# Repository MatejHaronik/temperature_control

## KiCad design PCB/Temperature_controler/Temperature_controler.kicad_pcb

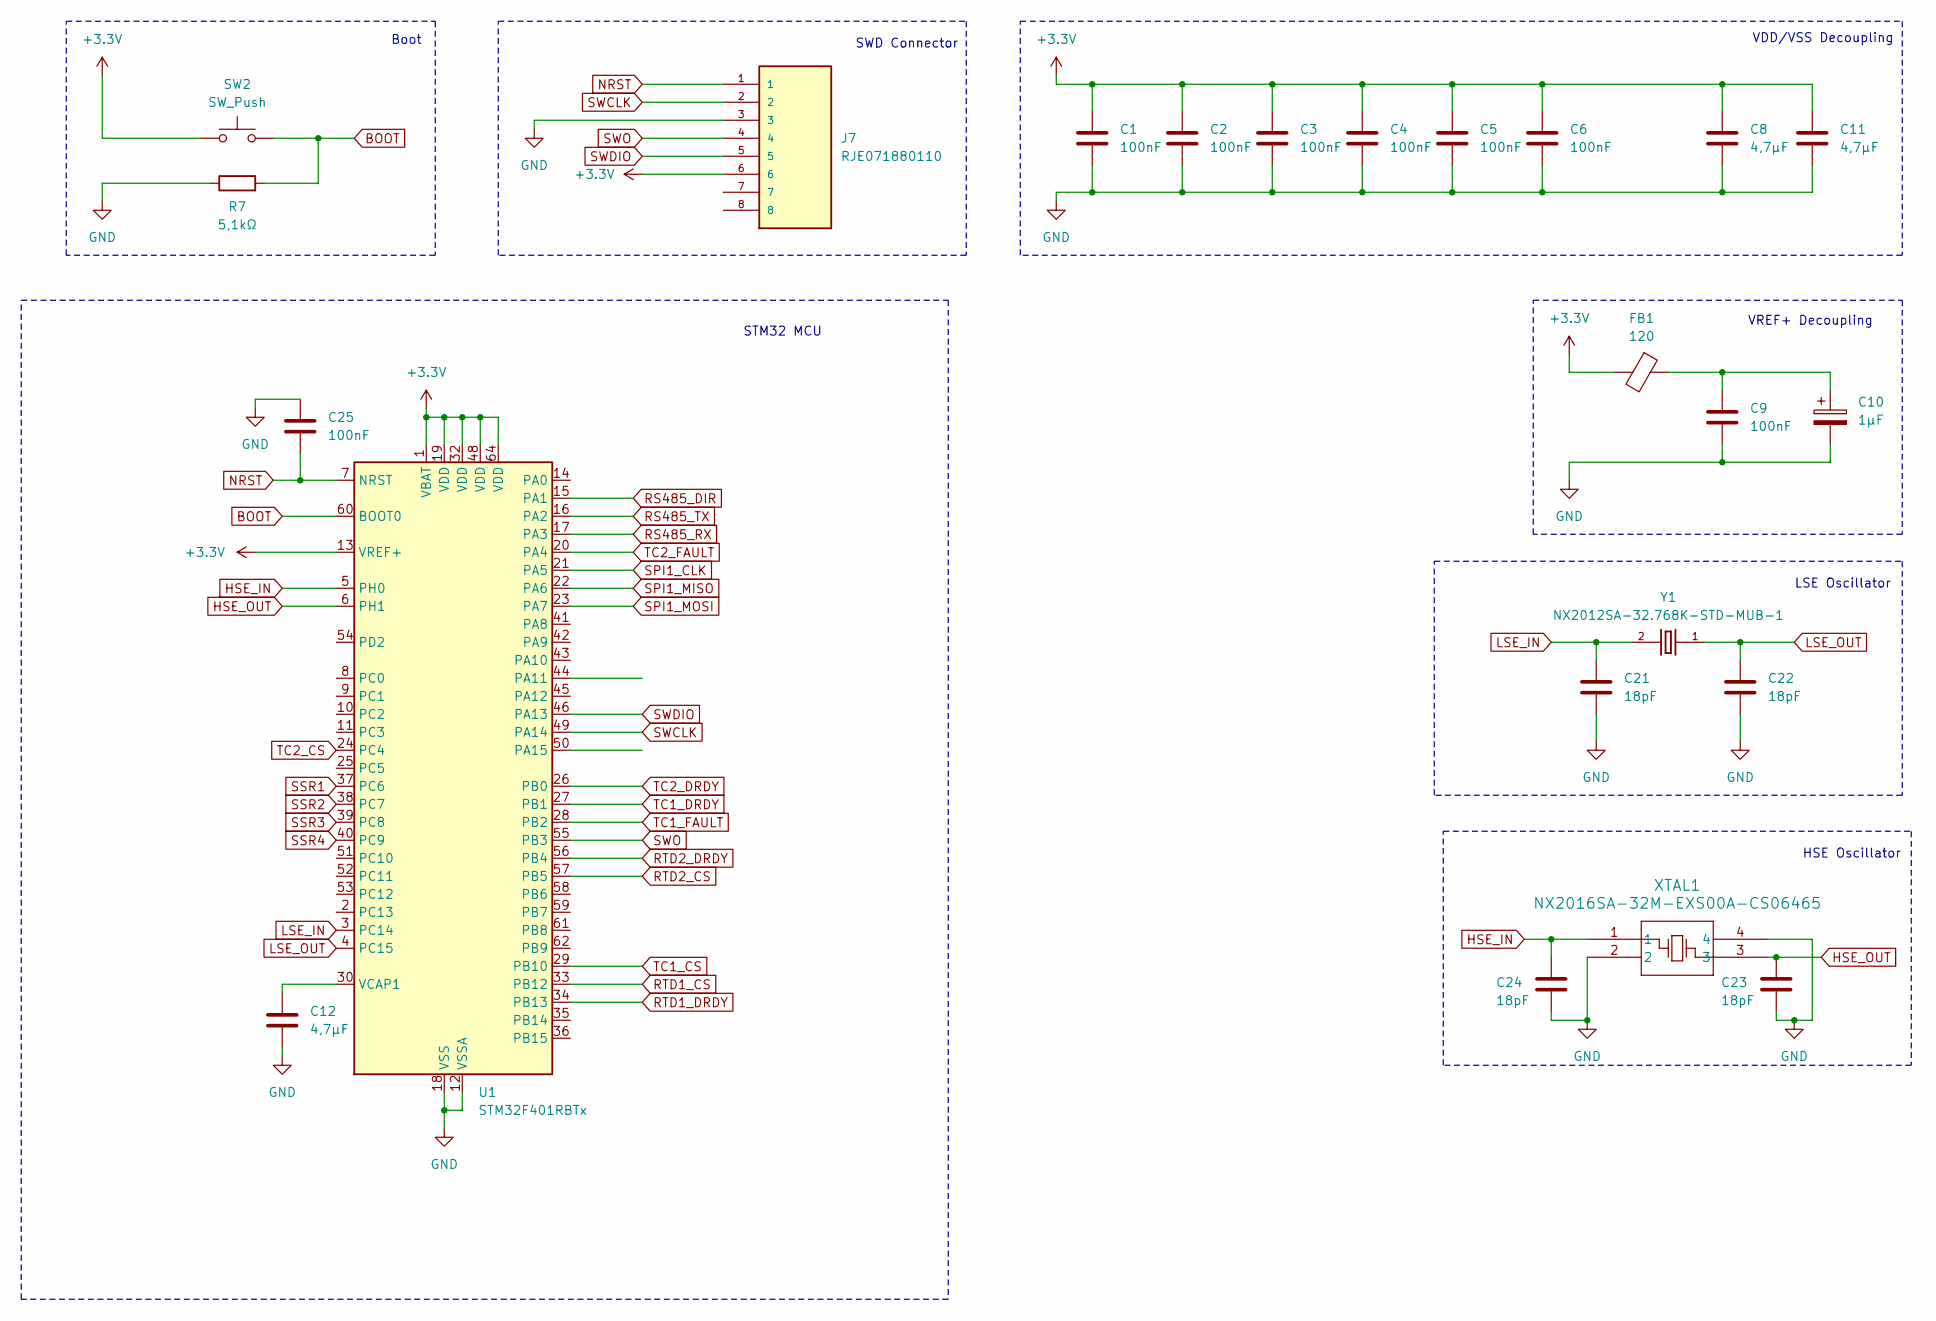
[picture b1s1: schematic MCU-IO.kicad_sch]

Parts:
C1, C2, C3, C4, C5, C6, C9, C25: 100nF; C_0805_2012Metric_Pad1.18x1.45mm_HandSolder
C8, C11, C12: 4,7µF; C_0805_2012Metric_Pad1.18x1.45mm_HandSolder
C10: 1µF; C_0805_2012Metric_Pad1.18x1.45mm_HandSolder
C21, C22, C23, C24: 18pF; C_0805_2012Metric_Pad1.18x1.45mm_HandSolder
FB1: 120; Fuse_2010_5025Metric_Pad1.52x2.65mm_HandSolder
J7: RJE071880110; AMPHENOL_RJE071880110; PARTREV C
R7: 5,1kΩ; R_0805_2012Metric_Pad1.20x1.40mm_HandSolder
SW2: SW_Push; SW_Push_1P1T-SH_NO_CK_KMR2xxG
U1: STM32F401RBTx; LQFP-64_10x10mm_P0.5mm
XTAL1: NX2016SA-32M-EXS00A-CS06465; NX2016SA_NDK
Y1: NX2012SA-32.768K-STD-MUB-1; XTAL_NX2012SA-32.768K-STD-MUB-1

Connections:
+3.3V: C1.1, C2.1, C3.1, C4.1, C5.1, C6.1, C8.1, C11.1, FB1.2, J7.6, SW2.1, U1.1 (VBAT), U1.13 (VREF+), U1.19 (VDD), U1.32 (VDD), U1.48 (VDD), U1.64 (VDD); also elsewhere on the board
BOOT: R7.2, SW2.2, U1.60 (BOOT0)
GND: C1.2, C2.2, C3.2, C4.2, C5.2, C6.2, C8.2, C9.2, C10.2, C11.2, C12.2, C21.2, C22.2, C23.2, C24.2, C25.1, J7.3, R7.1, U1.12 (VSSA), U1.18 (VSS), U1.31 (VSS), U1.47 (VSS), U1.63 (VSS), XTAL1.2, XTAL1.4; also elsewhere on the board
HSE_IN: C24.1, U1.5 (PH0), XTAL1.1
HSE_OUT: C23.1, U1.6 (PH1), XTAL1.3
LSE_IN: C21.1, U1.3 (PC14), Y1.2
LSE_OUT: C22.1, U1.4 (PC15), Y1.1
NRST: C25.2, J7.1, U1.7 (NRST)
unnamed: C9.1, C10.1, FB1.1
unnamed: C12.1, U1.30 (VCAP1)
RS485_DIR: U1.15 (PA1); also elsewhere on the board
RS485_RX: U1.17 (PA3); also elsewhere on the board
RS485_TX: U1.16 (PA2); also elsewhere on the board
RTD1_CS: U1.33 (PB12); also elsewhere on the board
RTD1_DRDY: U1.34 (PB13); also elsewhere on the board
RTD2_CS: U1.57 (PB5); also elsewhere on the board
RTD2_DRDY: U1.56 (PB4); also elsewhere on the board
SPI1_CLK: U1.21 (PA5); also elsewhere on the board
SPI1_MISO: U1.22 (PA6); also elsewhere on the board
SPI1_MOSI: U1.23 (PA7); also elsewhere on the board
SSR1: U1.37 (PC6); also elsewhere on the board
SSR2: U1.38 (PC7); also elsewhere on the board
SSR3: U1.39 (PC8); also elsewhere on the board
SSR4: U1.40 (PC9); also elsewhere on the board
SWCLK: J7.2, U1.49 (PA14)
SWDIO: J7.5, U1.46 (PA13)
SWO: J7.4, U1.55 (PB3)
TC1_CS: U1.29 (PB10); also elsewhere on the board
TC1_DRDY: U1.27 (PB1); also elsewhere on the board
TC1_FAULT: U1.28 (PB2); also elsewhere on the board
TC2_CS: U1.24 (PC4); also elsewhere on the board
TC2_DRDY: U1.26 (PB0); also elsewhere on the board
TC2_FAULT: U1.20 (PA4); also elsewhere on the board

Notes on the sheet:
HSE Oscillator
SWD Connector
LSE Oscillator
VREF+ Decoupling
Boot
STM32 MCU
VDD/VSS Decoupling

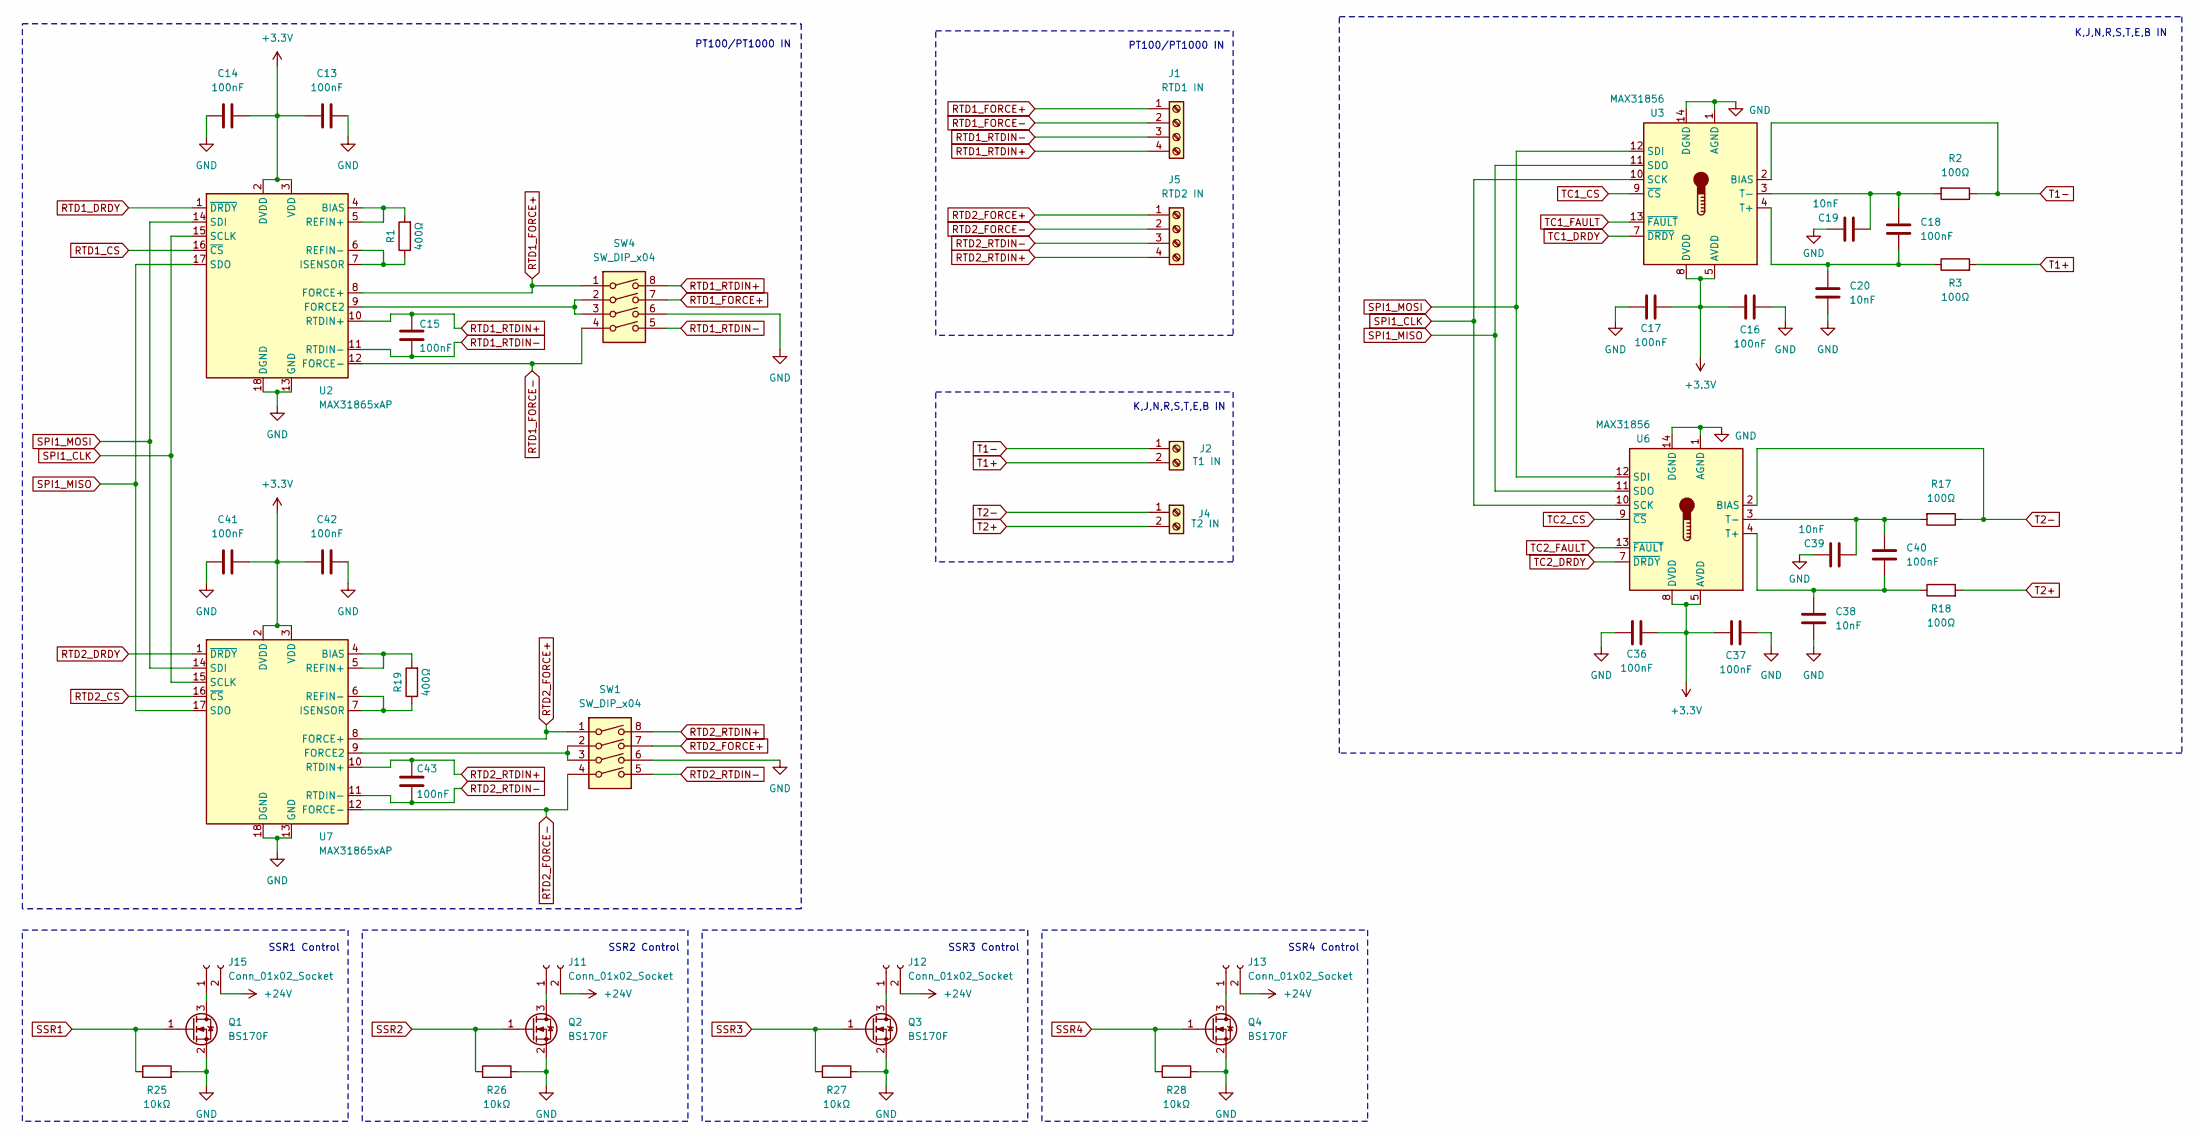
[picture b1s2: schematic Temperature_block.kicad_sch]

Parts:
C13, C14, C15, C16, C17, C18, C36, C37, C40, C41, C42, C43: 100nF; C_0805_2012Metric_Pad1.18x1.45mm_HandSolder
C19, C20, C38, C39: 10nF; C_0805_2012Metric_Pad1.18x1.45mm_HandSolder
J1: RTD1 IN; TerminalBlock_Phoenix_MKDS-1,5-4_1x04_P5.00mm_Horizontal
J2: T1 IN; TerminalBlock_Phoenix_MKDS-1,5-2_1x02_P5.00mm_Horizontal
J4: T2 IN; TerminalBlock_Phoenix_MKDS-1,5-2_1x02_P5.00mm_Horizontal
J5: RTD2 IN; TerminalBlock_Phoenix_MKDS-1,5-4_1x04_P5.00mm_Horizontal
J11, J12, J13, J15: Conn_01x02_Socket; SolderWire-1sqmm_1x02_P5.4mm_D1.4mm_OD2.7mm
Q1, Q2, Q3, Q4: BS170F; SOT-23
R1, R19: 400Ω; R_0805_2012Metric_Pad1.20x1.40mm_HandSolder
R2, R3, R17, R18: 100Ω; R_0805_2012Metric_Pad1.20x1.40mm_HandSolder
R25, R26, R27, R28: 10kΩ; R_0805_2012Metric_Pad1.20x1.40mm_HandSolder
SW1, SW4: SW_DIP_x04; SW_DIP_SPSTx04_Slide_Omron_A6H-4101_W6.15mm_P1.27mm
U2, U7: MAX31865xAP; SSOP-20_5.3x7.2mm_P0.65mm
U3, U6: MAX31856; TSSOP-14_4.4x5mm_P0.65mm

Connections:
+3.3V: C13.1, C14.1, C16.1, C17.1, C36.1, C37.1, C41.1, C42.1, U2.2 (DVDD), U2.3 (VDD), U3.5 (AVDD), U3.8 (DVDD), U6.5 (AVDD), U6.8 (DVDD), U7.2 (DVDD), U7.3 (VDD); also elsewhere on the board
+24V: J11.2, J12.2, J13.2, J15.2; also elsewhere on the board
GND: C13.2, C14.2, C16.2, C17.2, C19.1, C20.2, C36.2, C37.2, C38.2, C39.1, C41.2, C42.2, Q1.2 (S), Q2.2 (S), Q3.2 (S), Q4.2 (S), R25.2, R26.2, R27.2, R28.2, SW1.6, SW4.6, U2.13 (GND), U2.18 (DGND), U2.19 (GND), U3.1 (AGND), U3.14 (DGND), U6.1 (AGND), U6.14 (DGND), U7.13 (GND), U7.18 (DGND), U7.19 (GND); also elsewhere on the board
unnamed: J11.1, Q2.3 (D)
unnamed: J12.1, Q3.3 (D)
unnamed: J13.1, Q4.3 (D)
unnamed: J15.1, Q1.3 (D)
unnamed: R1.2, U2.4 (BIAS), U2.5 (REFIN+)
unnamed: SW4.2, SW4.3, U2.9 (FORCE2)
unnamed: R1.1, U2.6 (REFIN-), U2.7 (ISENSOR)
unnamed: C18.2, C20.1, R3.1, U3.4 (T+)
unnamed: C18.1, C19.2, R2.2, U3.3 (T-)
unnamed: C38.1, C40.2, R18.1, U6.4 (T+)
unnamed: C39.2, C40.1, R17.2, U6.3 (T-)
unnamed: R19.2, U7.4 (BIAS), U7.5 (REFIN+)
unnamed: SW1.2, SW1.3, U7.9 (FORCE2)
unnamed: R19.1, U7.6 (REFIN-), U7.7 (ISENSOR)
RTD1_CS: U2.16 (~CS); also elsewhere on the board
RTD1_DRDY: U2.1 (~DRDY); also elsewhere on the board
RTD1_FORCE+: J1.1, SW4.1, SW4.7, U2.8 (FORCE+)
RTD1_FORCE-: J1.2, SW4.4, U2.12 (FORCE-)
RTD1_RTDIN+: C15.2, J1.4, SW4.8, U2.10 (RTDIN+)
RTD1_RTDIN-: C15.1, J1.3, SW4.5, U2.11 (RTDIN-)
RTD2_CS: U7.16 (~CS); also elsewhere on the board
RTD2_DRDY: U7.1 (~DRDY); also elsewhere on the board
RTD2_FORCE+: J5.1, SW1.1, SW1.7, U7.8 (FORCE+)
RTD2_FORCE-: J5.2, SW1.4, U7.12 (FORCE-)
RTD2_RTDIN+: C43.2, J5.4, SW1.8, U7.10 (RTDIN+)
RTD2_RTDIN-: C43.1, J5.3, SW1.5, U7.11 (RTDIN-)
SPI1_CLK: U2.15 (SCLK), U3.10 (SCK), U6.10 (SCK), U7.15 (SCLK); also elsewhere on the board
SPI1_MISO: U2.17 (SDO), U3.11 (SDO), U6.11 (SDO), U7.17 (SDO); also elsewhere on the board
SPI1_MOSI: U2.14 (SDI), U3.12 (SDI), U6.12 (SDI), U7.14 (SDI); also elsewhere on the board
SSR1: Q1.1 (G), R25.1; also elsewhere on the board
SSR2: Q2.1 (G), R26.1; also elsewhere on the board
SSR3: Q3.1 (G), R27.1; also elsewhere on the board
SSR4: Q4.1 (G), R28.1; also elsewhere on the board
T1+: J2.2, R3.2
T1-: J2.1, R2.1, U3.2 (BIAS)
T2+: J4.2, R18.2
T2-: J4.1, R17.1, U6.2 (BIAS)
TC1_CS: U3.9 (~CS); also elsewhere on the board
TC1_DRDY: U3.7 (~DRDY); also elsewhere on the board
TC1_FAULT: U3.13 (~FAULT); also elsewhere on the board
TC2_CS: U6.9 (~CS); also elsewhere on the board
TC2_DRDY: U6.7 (~DRDY); also elsewhere on the board
TC2_FAULT: U6.13 (~FAULT); also elsewhere on the board

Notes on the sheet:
K,J,N,R,S,T,E,B IN
PT100/PT1000 IN
SSR2 Control
SSR4 Control
SSR3 Control
SSR1 Control

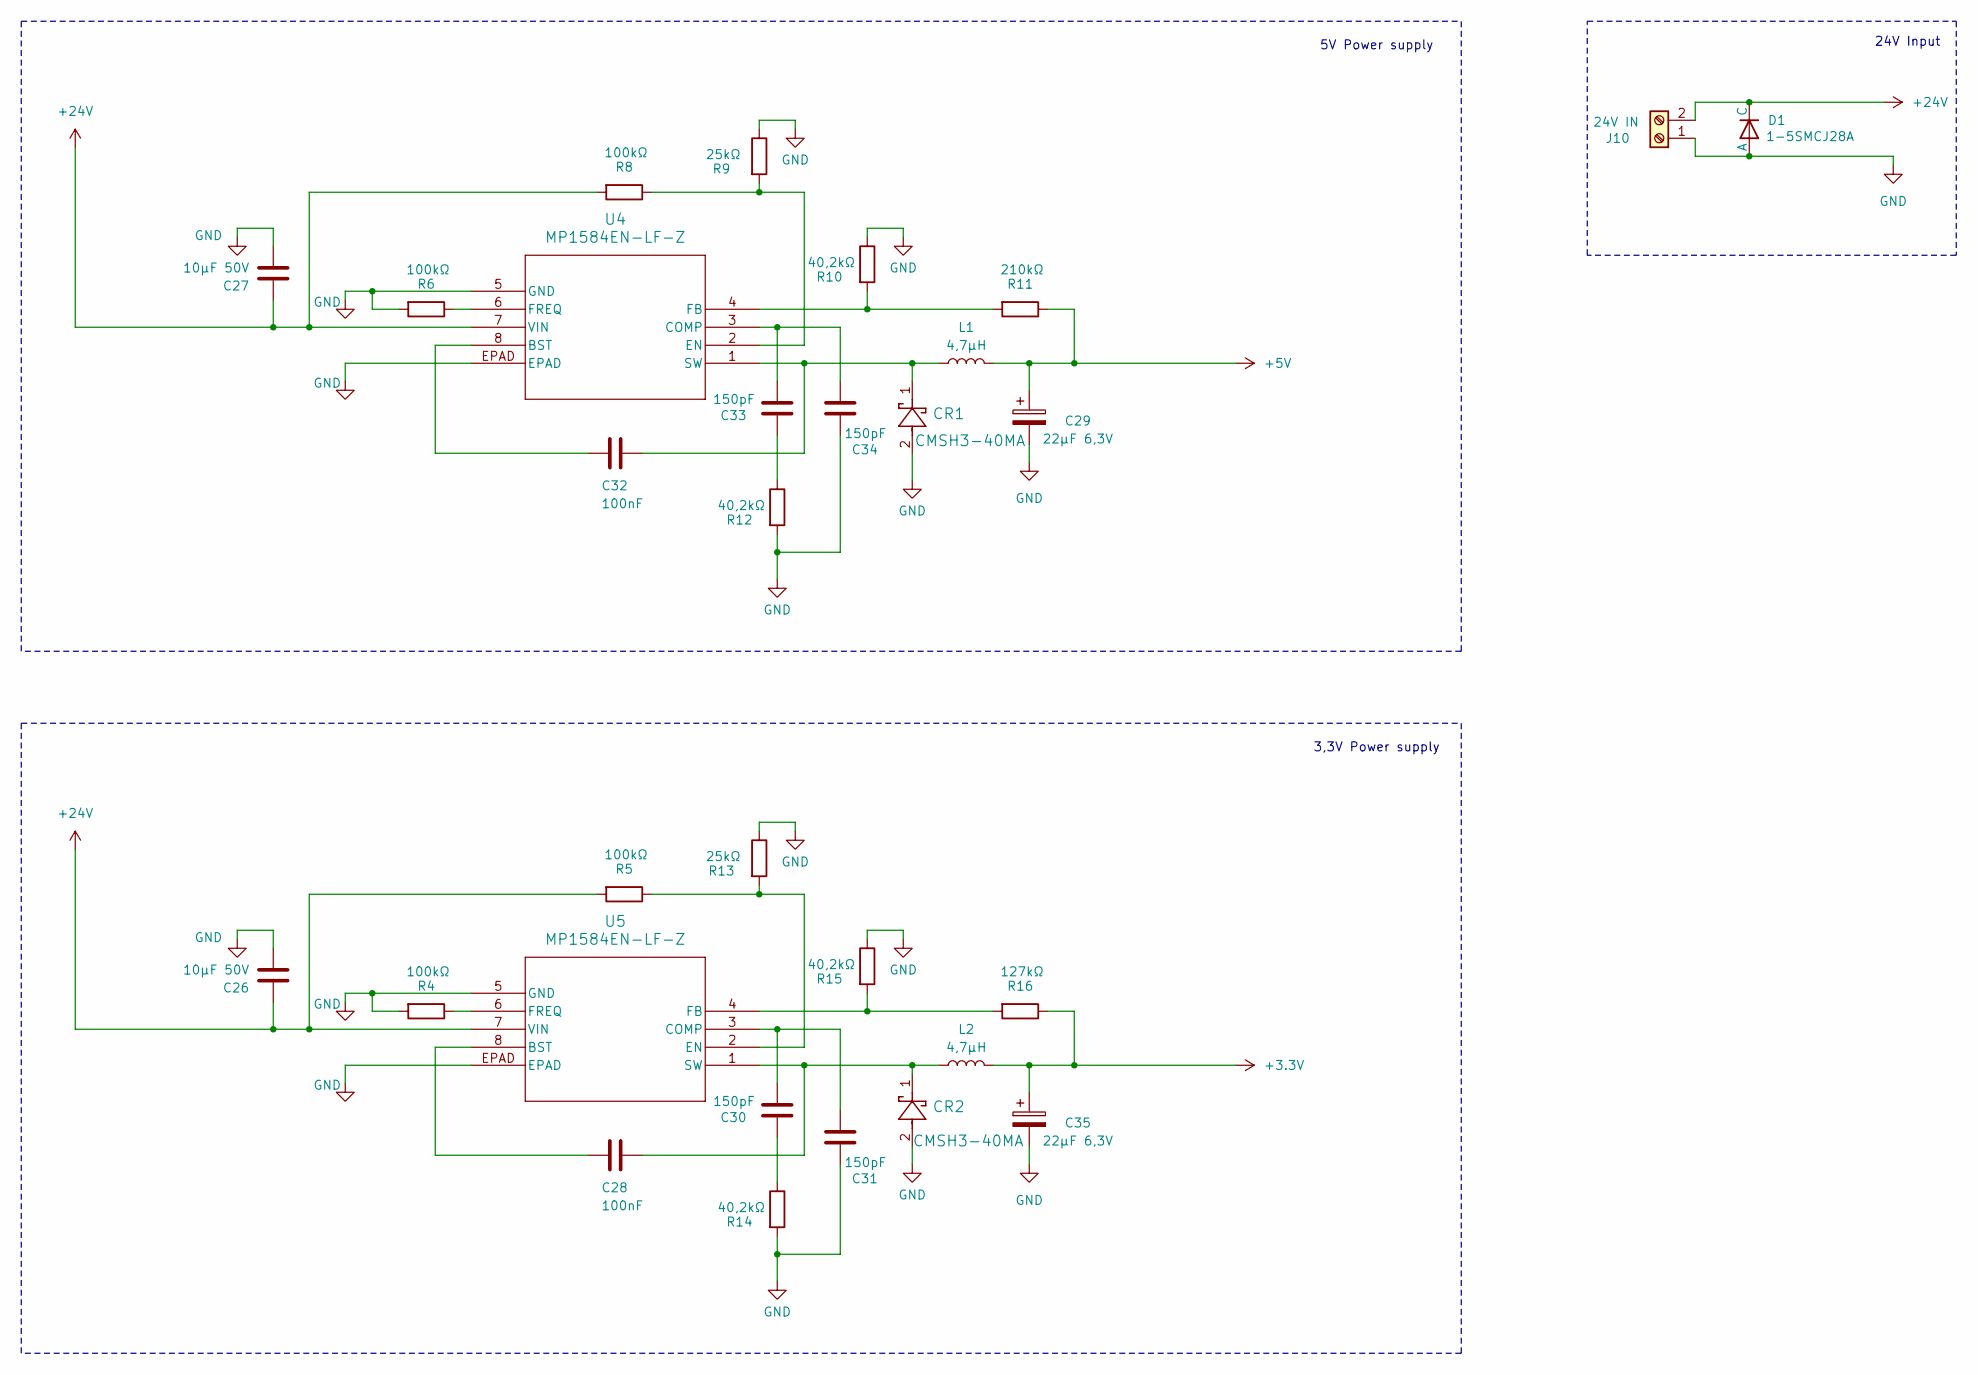
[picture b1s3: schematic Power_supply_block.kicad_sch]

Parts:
C26, C27: 10µF 50V; C_0805_2012Metric_Pad1.18x1.45mm_HandSolder
C28, C32: 100nF; C_0805_2012Metric_Pad1.18x1.45mm_HandSolder
C29, C35: 22µF 6,3V; C_0805_2012Metric_Pad1.18x1.45mm_HandSolder
C30, C31, C33, C34: 150pF; C_0805_2012Metric_Pad1.18x1.45mm_HandSolder
CR1, CR2: CMSH3-40MA; D_3220_8050Metric_Pad2.65x5.15mm_HandSolder
D1: 1-5SMCJ28A; D_1812_4532Metric_Pad1.30x3.40mm_HandSolder
J10: 24V IN; TerminalBlock_Phoenix_MKDS-1,5-2_1x02_P5.00mm_Horizontal
L1, L2: 4,7µH; L_0805_2012Metric_Pad1.05x1.20mm_HandSolder
R4, R5, R6, R8: 100kΩ; R_0805_2012Metric_Pad1.20x1.40mm_HandSolder
R9, R13: 25kΩ; R_0805_2012Metric_Pad1.20x1.40mm_HandSolder
R10, R12, R14, R15: 40,2kΩ; R_0805_2012Metric_Pad1.20x1.40mm_HandSolder
R11: 210kΩ; R_0805_2012Metric_Pad1.20x1.40mm_HandSolder
R16: 127kΩ; R_0805_2012Metric_Pad1.20x1.40mm_HandSolder
U4, U5: MP1584EN-LF-Z; SOIC-8-1EP_3.9x4.9mm_P1.27mm_EP2.41x3.3mm_ThermalVias

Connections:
+3.3V: C35.1, L2.2, R16.1; also elsewhere on the board
+5V: C29.1, L1.2, R11.1; also elsewhere on the board
+24V: C26.1, C27.1, D1.2 (C), J10.2, R5.2, R8.2, U4.7 (VIN), U5.7 (VIN); also elsewhere on the board
GND: C26.2, C27.2, C29.2, C31.2, C34.2, C35.2, CR1.2, CR2.2, D1.1 (A), J10.1, R4.2, R6.2, R9.1, R10.1, R12.2, R13.1, R14.2, R15.1, U4.5 (GND), U4.EPAD, U5.5 (GND), U5.EPAD; also elsewhere on the board
unnamed: C30.2, R14.1
unnamed: C33.2, R12.1
unnamed: C32.2, U4.8 (BST)
unnamed: C33.1, C34.1, U4.3 (COMP)
unnamed: R8.1, R9.2, U4.2 (EN)
unnamed: R10.2, R11.2, U4.4 (FB)
unnamed: R6.1, U4.6 (FREQ)
unnamed: C32.1, CR1.1, L1.1, U4.1 (SW)
unnamed: C28.2, U5.8 (BST)
unnamed: C30.1, C31.1, U5.3 (COMP)
unnamed: R5.1, R13.2, U5.2 (EN)
unnamed: R15.2, R16.2, U5.4 (FB)
unnamed: R4.1, U5.6 (FREQ)
unnamed: C28.1, CR2.1, L2.1, U5.1 (SW)

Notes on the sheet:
24V Input
5V Power supply
3,3V Power supply

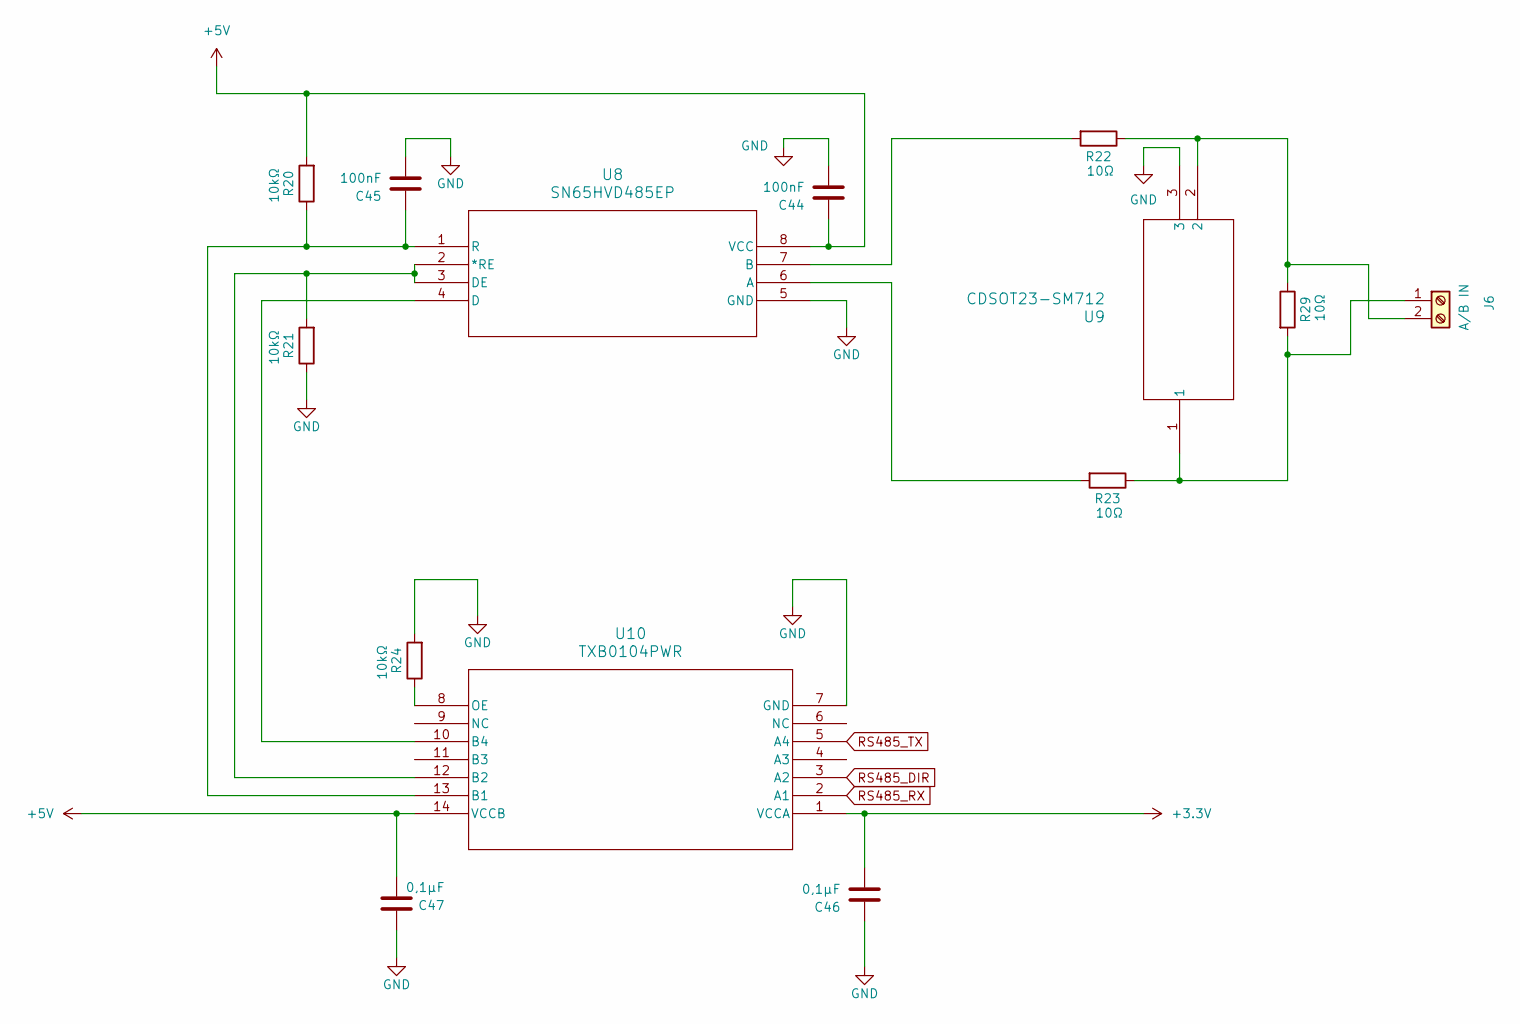
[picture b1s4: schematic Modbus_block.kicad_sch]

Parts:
C44, C45: 100nF; C_0805_2012Metric_Pad1.18x1.45mm_HandSolder
C46, C47: 0,1µF; C_0805_2012Metric_Pad1.18x1.45mm_HandSolder
J6: A/B IN; TerminalBlock_Phoenix_MKDS-1,5-2_1x02_P5.00mm_Horizontal
R20, R21, R24: 10kΩ; R_0805_2012Metric_Pad1.20x1.40mm_HandSolder
R22, R23, R29: 10Ω; R_0805_2012Metric_Pad1.20x1.40mm_HandSolder
U8: SN65HVD485EP; P8
U9: CDSOT23-SM712; SOT_SM712
U10: TXB0104PWR; PW14

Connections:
+3.3V: C46.2, U10.1 (VCCA); also elsewhere on the board
+5V: C44.1, C47.2, R20.2, U8.8 (VCC), U10.14 (VCCB); also elsewhere on the board
GND: C44.2, C45.2, C46.1, C47.1, R21.1, R24.2, U8.5 (GND), U9.3, U10.7 (GND); also elsewhere on the board
unnamed: J6.1, R23.1, R29.2, U9.1
unnamed: J6.2, R22.1, R29.1, U9.2
unnamed: R23.2, U8.6 (A)
unnamed: R22.2, U8.7 (B)
unnamed: C45.1, R20.1, U8.1 (R), U10.13 (B1)
unnamed: R21.2, U8.2 (*RE), U8.3 (DE), U10.12 (B2)
unnamed: U8.4 (D), U10.10 (B4)
unnamed: R24.1, U10.8 (OE)
RS485_DIR: U10.3 (A2); also elsewhere on the board
RS485_RX: U10.2 (A1); also elsewhere on the board
RS485_TX: U10.5 (A4); also elsewhere on the board

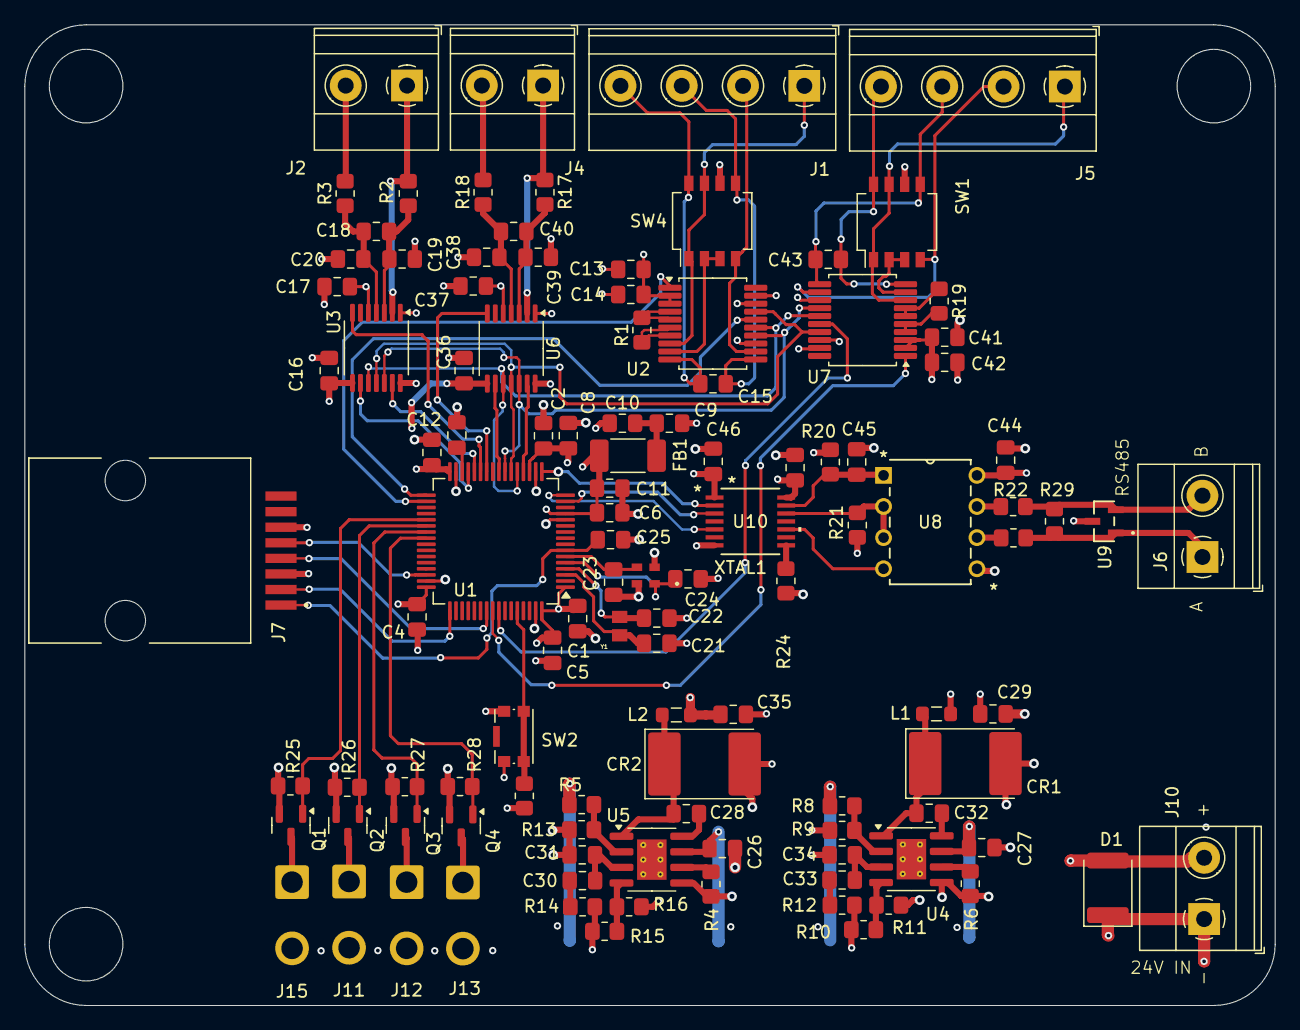
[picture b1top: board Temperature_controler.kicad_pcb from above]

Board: 4 copper layers, 102.0 x 80.0 mm, 111 parts (0 on the bottom side), 83 nets.

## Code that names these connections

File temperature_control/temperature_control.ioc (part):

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Mcu.Name=STM32G031K(4-6-8)Tx
Mcu.Package=LQFP32
Mcu.UserName=STM32G031K8Tx
PA1.GPIOParameters=GPIO_Speed,PinState
PA1.GPIO_Speed=GPIO_SPEED_FREQ_HIGH
PA1.Mode=Full_Duplex_Master
PA1.PinState=GPIO_PIN_RESET
PA1.Signal=SPI1_SCK
PA10.Mode=Asynchronous
PA10.Signal=USART1_RX
PA13.GPIOParameters=GPIO_Label
PA13.GPIO_Label=T_JTMS
PA13.Mode=Serial_Wire
PA13.Signal=SYS_SWDIO
PA14-BOOT0.GPIOParameters=GPIO_Label
PA14-BOOT0.GPIO_Label=T_JTCK
PA14-BOOT0.Mode=Serial_Wire
PA14-BOOT0.Signal=SYS_SWCLK
PA2.GPIOParameters=GPIO_PuPd,GPIO_Label
PA2.GPIO_Label=T_VCP_TX
PA2.GPIO_PuPd=GPIO_PULLUP
PA2.Mode=Asynchronous
PA2.Signal=USART2_TX
PA3.GPIOParameters=GPIO_PuPd,GPIO_Label
PA3.GPIO_Label=T_VCP_RX
PA3.GPIO_PuPd=GPIO_PULLUP
PA3.Mode=Asynchronous
PA3.Signal=USART2_RX
PA4.GPIOParameters=PinState
PA4.PinState=GPIO_PIN_SET
PA4.Signal=GPIO_Output
PA9.Mode=Asynchronous
PA9.Signal=USART1_TX
PB4.Mode=Full_Duplex_Master
PB4.Signal=SPI1_MISO
PB5.GPIOParameters=GPIO_Speed
PB5.GPIO_Speed=GPIO_SPEED_FREQ_HIGH
PB5.Mode=Full_Duplex_Master
PB5.Signal=SPI1_MOSI
PC14-OSC32_IN\ (PC14).Mode=LSE-External-Oscillator
PC14-OSC32_IN\ (PC14).Signal=RCC_OSC32_IN
PC15-OSC32_OUT\ (PC15).Mode=LSE-External-Oscillator
PC15-OSC32_OUT\ (PC15).Signal=RCC_OSC32_OUT
PC6.GPIOParameters=GPIO_Label
PC6.GPIO_Label=LD3 [Green]
PC6.Signal=GPIO_Output
PF2\ -\ NRST.GPIOParameters=GPIO_Label
PF2\ -\ NRST.GPIO_Label=T_NRST
PF2\ -\ NRST.Signal=GPXTI2
RCC.HSE_VALUE=8000000
RCC.SYSCLKFreq_VALUE=64000000
RCC.SYSCLKSource=RCC_SYSCLKSOURCE_PLLCLK
board=NUCLEO-G031K8
boardIOC=true

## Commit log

2025-05-09 Function driver
2025-05-15 Rebase lost connection
2025-05-15 Working prototype. Handling requests from modbus and sending temperature updates.
2025-05-19 Added FreeRTOS.
2025-05-20 Uart message blocking CPU bug.
2025-05-26 Added FreeRTOS branch
2025-05-26 First PCB prototype design
2025-05-26 PCB files initialization
2025-05-27 Modbus block added,temperature block edit
2025-06-03 PCB progress
2025-06-07 PCB layout progress and PDF for review added
2025-06-09 Schematic update, PCB progress
2025-06-11 PCB traces changed
2025-06-18 PCB update and sensor abstraction layer
